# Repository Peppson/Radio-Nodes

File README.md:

# radio-nodes

Solar/Battery/USB powered wireless "smarthome" modules, based on the Attiny824 microcontroller.  
Serves as the end-node of [MQTT-radio-gateway](https://github.com/Peppson/MQTT-radio-gateway).   
Written in C++ with PlatformIO framework.  

&nbsp;
## Project Overview
- Each node is easily configurable to perform various tasks, such as watering plants,   
turn on the coffeemaker, opening blinds, relaying sensor data, etc. 

- Power consumption was the main concern when designing this.   
Nodes consumes ∼`2mA` @ 3.3V in active mode, and as low as ∼`3uA` @ 3.3V while deepsleeping!  
Making it possible to power the nodes indefinitely from a small solarpanel.  
Measured and optimized using [Power Profiler Kit II](https://www.nordicsemi.com/Products/Development-hardware/Power-Profiler-Kit-2).  

- This project was primarily made for personal ***"needs"***. But it is open for use by anyone who finds it beneficial.  
Every ***node*** has it's own directory inside `src` and it's own enviroment, selected from `platformio.ini`.

&nbsp;
## Hardware and PCB  
Designed a compact PCB integrating a [TP4056](https://www.amazon.com/TP4056/s?k=TP4056) Li-ion/LiPo battery charger, an [NRF24L01+](https://www.amazon.com/s?k=nRF24L01%2B&crid=1VM0GXMUG7ISX&sprefix=nrf24l01%2B%2Caps%2C145&ref=nb_sb_noss_1) radio,   
and the [Attiny824](https://www.mouser.se/ProductDetail/Microchip-Technology/ATTINY824-SSF?qs=pUKx8fyJudA6%2F%2FVSNIlI1w%3D%3D) AVR microcontroller.  

KiCad files: [📂 _KiCad/](./_KiCad/)  
More images in: [📂 _images/](./_images/)  
&nbsp;
> [!WARNING]
> Current PCB is wrong. Q1, Q2 and Q3 are incorrectly connected. Will update soon™

&nbsp;
<details>
<summary>
    Schematic
</summary>  

&nbsp;

</details>

<details>
<summary>
    PCB layout 
</summary>  

&nbsp;
> 2-layer PCB, dimensions 42mm x 31mm.

</details>  

<details>
<summary>
    Power consumption in active mode 
</summary>  

&nbsp; 
> In active mode, the node toggles its radio `on` for 50ms and `off` for 950ms to minimize power usage.

</details>
  
#### PCB

#### Hardware

&nbsp;
## Nodes 
<details>
<summary>
    Nodes 1-10: Self watering plants (Solar/USB powered)  
</summary>

Uses a 3-5V waterpump and DIY capacative fluid-level sensor.  See link below.  
[Liquid Level Sensing Using Capacitive-to-Digital Converters](https://www.analog.com/en/analog-dialogue/articles/liquid-level-sensing-using-cdcs.html)  

The solar-powered variant uses the TP4056 to charge a 3.7V Li-ion/LiPo battery.  
While the USB variant skips that step and plugs directly into 5V (3.3V LDO onboard).  

#### Node 1 hardware:  

&nbsp;  

#### Node 1 water sensor linearity:    

> Sensor (Adc) readings vs water level in %. 

&nbsp;  
</details>

<details>
    <summary>
        Node 11: Mocca Master controller
    </summary>

Uses a SG90 servo mounted internally to toggle the `On/Off` button,   
and a hall-effect current sensor, to get the current state.  
> "Looks pretty neat when the button toggles all by itself :)"   

</details>

&nbsp;

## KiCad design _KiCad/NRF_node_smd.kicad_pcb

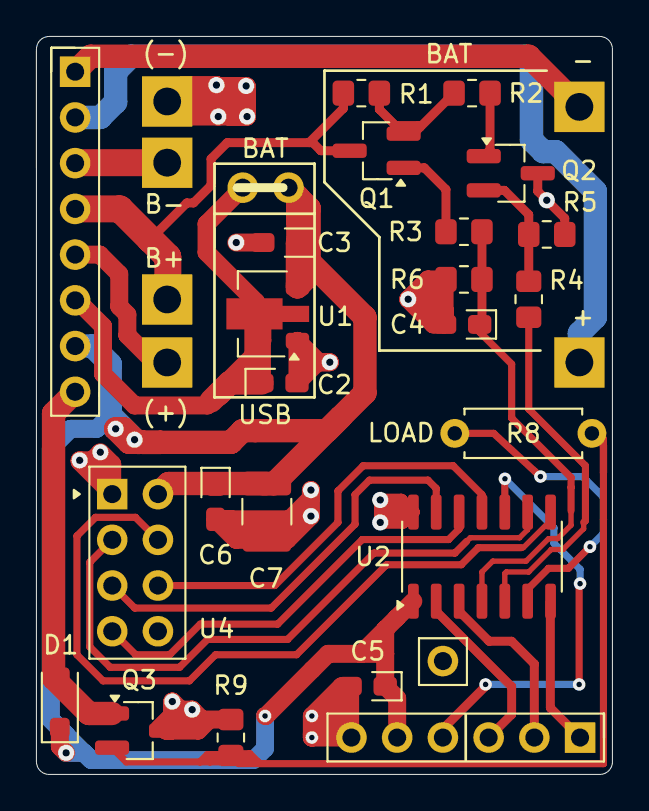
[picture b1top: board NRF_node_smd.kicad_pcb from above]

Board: 2 copper layers, 32.0 x 41.0 mm, 23 parts (0 on the bottom side), 22 nets.

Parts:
C2, C3: 1uf; CP_EIA-2012-15_AVX-P_Pad1.30x1.05mm_HandSolder
C4, C5, C6: 100nF; CP_EIA-2012-15_AVX-P_Pad1.30x1.05mm_HandSolder
C7: 22uF; C_1210_3225Metric_Pad1.33x2.70mm_HandSolder
D1: D; D_SOD-123F
J6: Conn_01x06; PinHeader_1x06_P2.54mm_Vertical
Q1: NTR4101PT1G; SOT-23_Handsoldering
Q2, Q3: PMV16XNR; SOT-23_Handsoldering
R1, R5: 100K; R_0805_2012Metric_Pad1.20x1.40mm_HandSolder
R2, R4, R6, R9: 10K; R_0805_2012Metric_Pad1.20x1.40mm_HandSolder
R3: 3K3; R_0805_2012Metric_Pad1.20x1.40mm_HandSolder
R8: 0-10K ?; R_Axial_DIN0207_L6.3mm_D2.5mm_P7.62mm_Horizontal
TP4056: TP4056-18650
U1: MCP1700T-3302E/MB; SOT-89-3
U2: ATtiny84A-P; SOIC-14_3.9x8.7mm_P1.27mm
U4: NRF24L01_Breakout; nRF24L01_Breakout

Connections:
/CE: U2.9 (PB0), U4.3 (CE)
/MISO: U2.12 (PA2), U4.7 (MISO)
/MOSI: U2.11 (PA1), U4.6 (MOSI)
/SCK: U2.13 (PA3), U4.5 (SCK)
/SS: U2.8 (PB1), U4.4 (~CSN)
ADC_ENABLED: R4.1, U2.5 (PA7)
ADC_MEASURE: C4.1, R3.2, R6.1, U2.4 (PA6)
BATTERY_VOLT: Q1.3 (S), R1.1, TP4056.5 (BAT(+))
GND: C2.2, C3.2, C4.2, C5.2, C6.2, C7.2, J6.6, Q2.3 (S), Q3.3 (S), R5.2, R6.2, R9.2, TP4056.3 (GND), U1.1 (GND), U2.14 (GND), U4.1 (GND)
LOAD_DRIVER_PIN: R8.1, U2.6 (PB3)
unnamed: D1.2 (A), Q3.1 (D)
unnamed: C2.1, U1.2 (VI)
unnamed: Q1.1 (D), R3.1
unnamed: Q1.2 (G), R1.2, R2.1
unnamed: Q2.1 (D), R2.2
unnamed: Q2.2 (G), R4.2, R5.1
unnamed: Q3.2 (G), R8.2, R9.1
PB2: J6.1, U2.7 (PB2)
PB4: J6.3, U2.2 (PA4)
PB5: J6.2, U2.3 (PA5)
UPDI: J6.4, U2.10 (~RESET/PA0)
VCC: C3.1, C5.1, C6.1, C7.1, D1.1 (K), J6.5, U1.3 (VO), U2.1 (VCC), U4.2 (VCC)

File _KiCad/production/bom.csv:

Designator,Footprint,Quantity,Value,LCSC Part #
"C2, C3",CP_EIA-2012-15_AVX-P_Pad1.30x1.05mm_HandSolder,2,1uf,
"C4, C5, C6",CP_EIA-2012-15_AVX-P_Pad1.30x1.05mm_HandSolder,3,100nF,
C7,1210,1,22uF,
D1,D_SOD-123F,1,D,
J6,PinHeader_1x06_P2.54mm_Vertical,1,Conn_01x06,
Q1,SOT-23_Handsoldering,1,NTR4101PT1G ,
"Q2, Q3",SOT-23_Handsoldering,2,PMV16XNR ,
"R1, R5",0805,2,100K,
"R2, R4, R6, R9",0805,4,10K,
R3,0805,1,3K3,
R8,R_Axial_DIN0207_L6.3mm_D2.5mm_P7.62mm_Horizontal,1,0-10K ?,
TP4056,TP4056-18650,1,~,
U1,SOT-89-3,1,MCP1700T-3302E/MB ,
U2,SOIC-14_3.9x8.7mm_P1.27mm,1,ATtiny84A-P,
U4,nRF24L01_Breakout,1,NRF24L01_Breakout,

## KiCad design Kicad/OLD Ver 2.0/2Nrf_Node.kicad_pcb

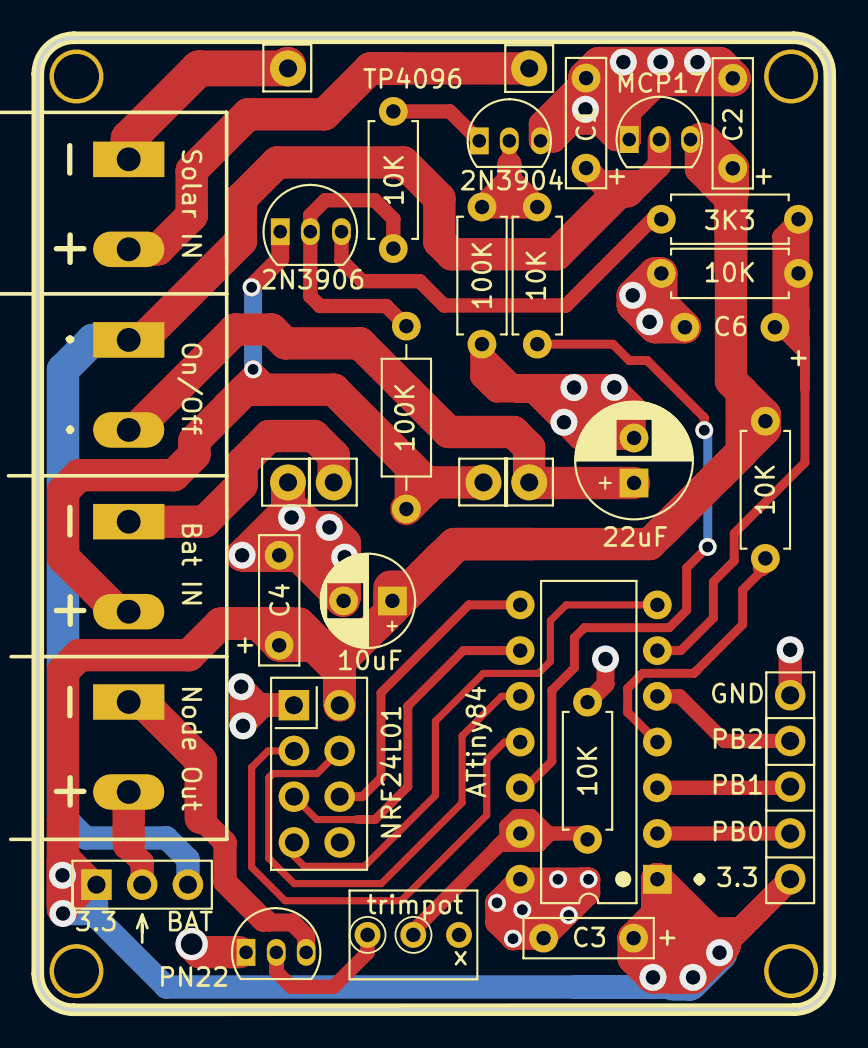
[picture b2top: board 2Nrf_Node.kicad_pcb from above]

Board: 2 copper layers, 44.0 x 54.0 mm, 32 parts (0 on the bottom side), 26 nets.

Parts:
10K: 10K; R_Axial_DIN0207_L6.3mm_D2.5mm_P7.62mm_Horizontal
C1, C2: 1uf; C_Rect_L7.0mm_W2.0mm_P5.00mm
C3, C4, C6: 100nF; C_Rect_L7.0mm_W2.0mm_P5.00mm
C5: 22uF; CP_Radial_D6.3mm_P2.50mm
C7: 10uF; CP_Radial_D5.0mm_P2.50mm
H1, H2, H4, H4#2: MountingHole; TestPoint_Keystone_5010-5014_Multipurpose
J1, J2, J3, J4: Terminal Block; TerminalBlock_Altech_AK300-2_P5.00mm
Pins: PinHeader_1x03_P2.54mm_Vertical
Q1: PN2222A; TO-92_Inline
Q2: 2N3906; TO-92_Inline
Q3: 2N3904; TO-92_Inline
R1: 3K3; R_Axial_DIN0207_L6.3mm_D2.5mm_P7.62mm_Horizontal
R2, R3, R6, R9: 10K; R_Axial_DIN0207_L6.3mm_D2.5mm_P7.62mm_Horizontal
R7: 100K; R_Axial_DIN0207_L6.3mm_D2.5mm_P7.62mm_Horizontal
R8: 100K; R_Axial_DIN0207_L6.3mm_D2.5mm_P10.16mm_Horizontal
SW2: SW_SPDT; PinHeader_1x03_P2.54mm_Vertical
TP4056: TP4056-Module
U1: MCP1700x-330xxTO; TO-92_Inline
U2: ATtiny84A-P; DIP-14_W7.62mm
U3: NRF24L01_Breakout; nRF24L01_Breakout

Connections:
1234: Q3.1 (E), R9.2
+3.3V: 10K.2, C2.1, C3.1, C4.1, C7.1, Pins.5, SW2.1 (A), U1.3 (VO), U2.1 (VCC), U3.2 (VCC)
/CE: U2.11 (PA2), U3.3 (CE)
/CSN: U2.10 (PA3), U3.4 (~CSN)
/MISO: U2.7 (PA6), U3.7 (MISO)
/MOSI: U2.8 (PA5), U3.6 (MOSI)
/SCK: U2.9 (PA4), U3.5 (SCK)
ADC_Enable: R6.1, U2.12 (PA1)
ADC_Measure: C6.1, R1.2, R2.1, U2.6 (PA7)
BAT_-: J3.1, TP4056.6 (VCC_OUT)
BAT_V: Q2.1 (E), R8.1, TP4056.5 (BAT(+))
GND: C1.2, C2.2, C3.2, C4.2, C5.2, C6.2, C7.2, Pins.1, Q1.1 (E), Q3.3 (C), R2.2, R3.1, R7.2, TP4056.4 (BAT(-)), U1.1 (GND), U2.14 (GND), U3.1 (GND)
unnamed: J4.2, SW2.2 (B)
unnamed: J4.1, Q1.3 (C)
unnamed: Pins.2, U2.5 (PB2)
unnamed: Pins.4, U2.2 (XTAL1/PB0)
unnamed: Pins.3, U2.3 (XTAL2/PB1)
unnamed: R3.2, U2.13 (AREF/PA0)
unnamed: Q2.2 (B), R8.2, R9.1
unnamed: Q2.3 (C), R1.1
unnamed: Q3.2 (B), R6.2, R7.1
unnamed: 10K.1, U2.4 (~RESET/PB3)
tp_+: J1.2, TP4056.1 (VCC_IN)
tp_-: J1.1, TP4056.2 (GND)
tp_out_+: C5.1, J2.2, TP4056.3 (GND)
tp_out_++: C1.1, J2.1, SW2.3 (C), U1.2 (VI)

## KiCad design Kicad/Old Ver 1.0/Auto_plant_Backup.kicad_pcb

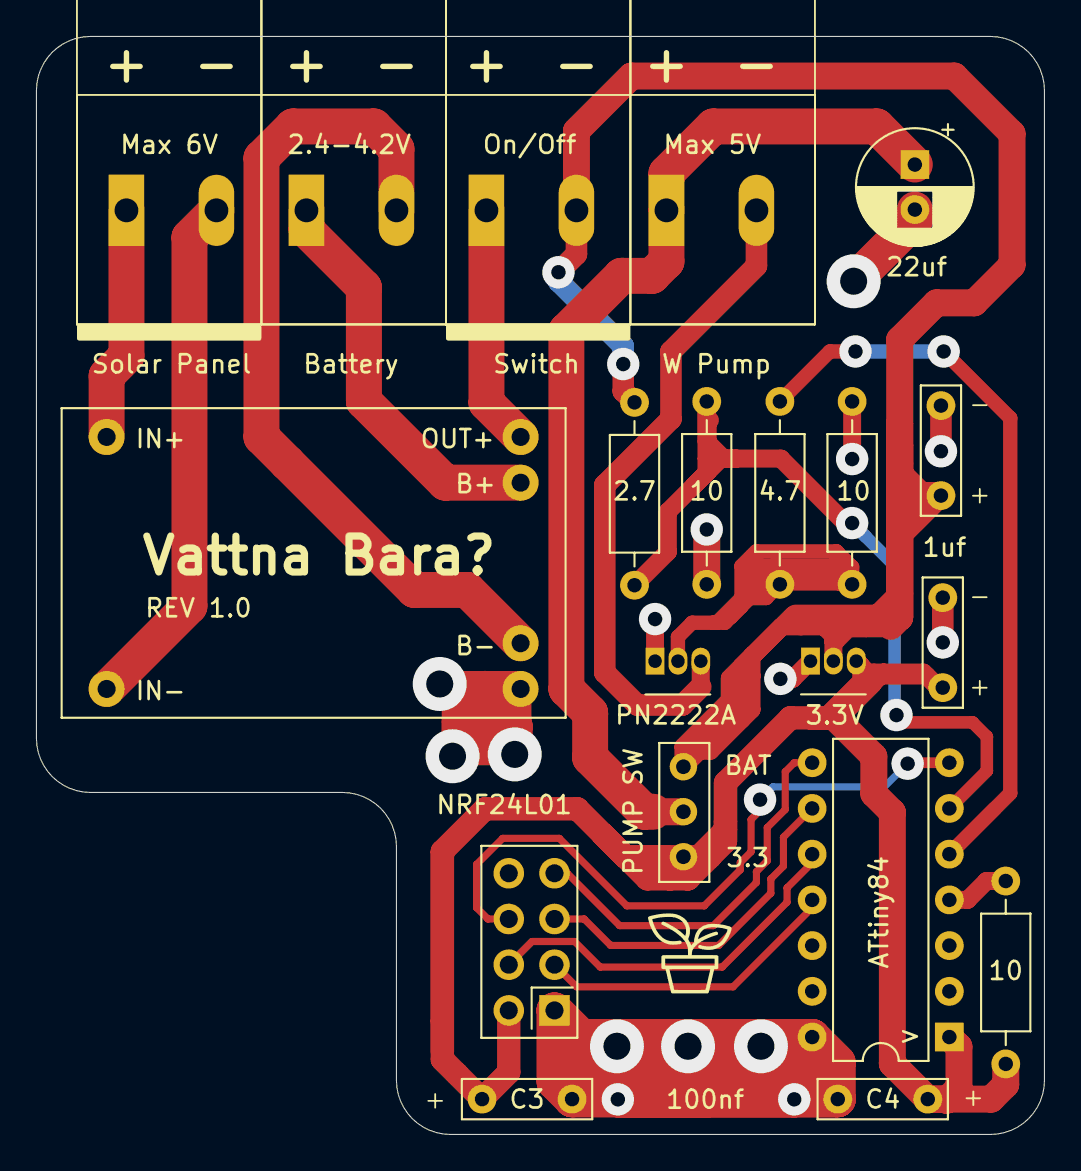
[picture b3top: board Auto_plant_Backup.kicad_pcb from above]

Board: 2 copper layers, 56.0 x 61.0 mm, 20 parts (0 on the bottom side), 19 nets.

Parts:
2.7: 2.7k; R_Axial_DIN0207_L6.3mm_D2.5mm_P10.16mm_Horizontal
3.3V: MCP1700x-330xxTO; TO-92_Inline
4.7, 10#3: 4.7k; R_Axial_DIN0207_L6.3mm_D2.5mm_P10.16mm_Horizontal
10, 10#2: 10k; R_Axial_DIN0207_L6.3mm_D2.5mm_P10.16mm_Horizontal
22uf: CP_Radial_D6.3mm_P2.50mm
100nf: 100nf; C_Rect_L7.0mm_W2.0mm_P5.00mm
+: Switch; TerminalBlock_Altech_AK300-2_P5.00mm
+#2: W Pump; TerminalBlock_Altech_AK300-2_P5.00mm
+#3: Battery; TerminalBlock_Altech_AK300-2_P5.00mm
-: Solar Panel; TerminalBlock_Altech_AK300-2_P5.00mm
ATtiny84: DIP-14_W7.62mm
C1, C2: 1uf; C_Rect_L7.0mm_W2.0mm_P5.00mm
C4: 100nf; C_Rect_L7.0mm_W2.0mm_P5.00mm
NRF24L01: NRF24L01_Breakout; nRF24L01_Breakout
PN2222A: PN2222A; TO-92_Inline
SW2: SW_SPDT; 2_way_switch
TP4056: TP4056-Module

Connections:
+3.3V: 3.3V.3 (VO), 10#3.2, 100nf.1, ATtiny84.1, C2.1, C4.1, NRF24L01.2 (VCC), SW2.1 (A)
/CE: ATtiny84.11, NRF24L01.3 (CE)
/MISO: ATtiny84.8, NRF24L01.7 (MISO)
/MOSI: ATtiny84.7, NRF24L01.6 (MOSI)
/SCK: ATtiny84.9, NRF24L01.5 (SCK)
BAT_V: 2.7.1, 3.3V.2 (VI), +.2, C1.1, SW2.3 (C)
CSN: ATtiny84.10, NRF24L01.4 (~CSN)
GND: 3.3V.1 (GND), 10.2, 10#2.2, 22uf.2, 100nf.2, ATtiny84.14, C1.2, C2.2, C4.2, NRF24L01.1 (GND), PN2222A.1 (E), TP4056.4 (BAT(-))
unnamed: -.2, TP4056.2 (GND)
unnamed: -.1, TP4056.1 (VCC_IN)
unnamed: +#3.2, TP4056.6 (VCC_OUT)
unnamed: +#3.1, TP4056.5 (BAT(+))
unnamed: +.1, TP4056.3 (GND)
unnamed: +#2.2, PN2222A.3 (C)
unnamed: 4.7.2, 10#2.1, PN2222A.2 (B)
unnamed: 4.7.1, ATtiny84.5
PA1: 2.7.2, 10.1, ATtiny84.6
P_OUT: 22uf.1, +#2.1, SW2.2 (B)
RESET: 10#3.1, ATtiny84.RESET

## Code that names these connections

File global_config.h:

#pragma once 
#include <Arduino.h>
#include <avr/io.h>
#include <avr/sleep.h>
#include <avr/wdt.h>
#include <avr/interrupt.h>
#include <stdint.h>


// Dev
#define USB_SERIAL_ENABLED 0                                // Serial TX 
#define DEBUG_LOOP_ENABLED 0                                // Enter debug_loop()
#define ADC_CAL_ENABLED 0                                   // Battery ADC calibration
#define PUMP_CAL_ENABLED 0                                  // Water pump calibration
#define SERVO_CAL_ENABLED 0                                 // Servo calibration
#define WATCHDOG_ENABLED 1                                  // Onboard Watchdog

// NRF24L01+ radio
#define RF24_THIS_ADDRESS NODE_ID                           // Radio address (env var from platformio.ini)
#define RF24_MASTER_ADDRESS 0                               // Address of master (0)
#define RF24_ON_TIME 50                                     // Active
#define RF24_OFF_TIME 950                                   // Sleeping                                  
#define RF24_CHANNEL 120                                    // Channel 1-126 (check with RF24/examples/scanner/scanner.ino) (120)
#define RF24_OUTPUT (RF24_PA_MAX)                           // Output level: RF24_PA_MIN, RF24_PA_LOW, RF24_PA_HIGH, RF24_PA_MAX, ERROR
#define RF24_DATARATE (RF24_250KBPS)                        // Datarate: RF24_2MBPS, RF24_1MBPS, RF24_250KBPS
#define RF24_PIPE 1                                         // Pipe address (1)

// Misc
#define SLEEP_RTC_INTERVAL_SECONDS 64.299f                  // Calibrated Average time between RTC interrupts while deepsleeping (s)
#define WATER_PUMP_RUNTIME_MAX 10                           // Maximum time the waterpump is allowed to run (s) if a flowerpot node


/*
-------------------------- ATtiny824 Pinout --------------------------                                   

                         VCC  1|o   |14 GND                        
             PWM/ADC --- PA4  2|    |13 PA3 --- RF24 SCK          
             PWM/ADC --- PA5  3|    |12 PA2 --- RF24 MISO  
                 ADC --- PA6  4|    |11 PA1 --- RF24 MOSI           
                 ADC --- PA7  5|    |10 PA0 --- UPDI programming          
           Power I/O --- PB3  6|    |9  PB0 --- RF24 CE          
       TX Serial out --- PB2  7|    |8  PB1 --- RF24 CSN  

----------------------------------------------------------------------
*/
#define PIN_CE                  PIN_PB0         // Nrf24l01 Ce pin
#define PIN_CSN                 PIN_PB1         // Nrf24l01 CSN pin
#define PIN_UPDI                PIN_PB0         // UPDI programming
#define PIN_POWER_IO            PIN_PB3         // Controls the "power circuit" (battery > load > Nfet > gnd)
#define PIN_TX_SERAIL           PIN_PB2         // Serial out TX


// Watchdog
#if WATCHDOG_ENABLED
    #define WDT_FEED() __asm__ __volatile__ ("wdr") 
    #define WDT_ENABLE() _PROTECTED_WRITE(WDT.CTRLA, WDT_PERIOD_4KCLK_gc)
    #define WDT_DISABLE() wdt_disable()
#else
    #define WDT_FEED()
    #define WDT_ENABLE()
    #define WDT_DISABLE()
#endif


// Logging
#if USB_SERIAL_ENABLED
    #define log(...) Serial.printf(__VA_ARGS__)
    #define STOP log("\n-----  STOP  ----- \n"); while (1) { WDT_FEED(); delay(1000); }
#else
    #define log(...)
    #define STOP
#endif


// Include selected node's "node_config.h" into global space (a bit hacky?)
#if NODE_ID == 1
    #include "src/01_solar_self_watering_plant/node_config.h"
#elif NODE_ID == 2
    #include "src/02_solar_self_watering_plant/node_config.h"
#elif NODE_ID == 3
    #include "src/03_solar_self_watering_plant/node_config.h"
#elif NODE_ID == 5
    #include "src/05_USB_self_watering_plant/node_config.h"
#elif NODE_ID == 6
    #include "src/06_USB_self_watering_plant/node_config.h"
#elif NODE_ID == 7
    #include "src/07_USB_self_watering_plant/node_config.h"
#elif NODE_ID == 11
    #include "src/11_moccamaster/node_config.h"
#elif NODE_ID == 255
    // Debug
#else
    #error "Unknown NODE_ID, check platformio.ini"
#endif


// CALIBRATION true if any if the calibration macros are set
#if DEBUG_LOOP_ENABLED || ADC_CAL_ENABLED || PUMP_CAL_ENABLED || SERVO_CAL_ENABLED
    #define CALIBRATION true
#else 
    #define CALIBRATION false
#endif

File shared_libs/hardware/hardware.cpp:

#include "hardware.h"
#include "utility.h"
#include "../shared_libs/rf24_radio/rf24_radio.h"


// Members
uint32_t Hardware::deepsleep_timestamp = 0; 
uint32_t Hardware::send_data_timestamp = 0;    
uint8_t Hardware::pin_ADC_enable;
uint8_t Hardware::pin_ADC_measure;
RF24Radio* Hardware::_radio_ptr;
volatile bool _lightsleep_wakeup;


// RTC Interrupt handler. Wakes up the CPU periodically while deepsleeping
// Only way to timekeep while deepsleeping
ISR (RTC_CNT_vect) {
    RTC.INTFLAGS |= RTC_OVF_bm;
    _lightsleep_wakeup = true;
}


// Helper
constexpr uint32_t convert_hhmm_to_seconds(const uint32_t& value) {
    static_assert(selected_node::SLEEP_AT_THIS_TIME >= 0 
        && selected_node::SLEEP_AT_THIS_TIME <= 2400, "Node time must follow \"hhmm\" format");

    uint32_t hour = value / 100;  
    uint32_t minute = value % 100; 

    return (hour*60*60) + (minute*60);
}


void Hardware::begin(RF24Radio* radio_ptr) {
    #if USB_SERIAL_ENABLED
        init_USB_serial();
    #endif

    // Helps with uploading if CPU is stuck "RSP_ILLEGAL_MCU_STATE"
    delay(3000);

    // Enable Watchdog at max interval ≈ 4s 
    WDT_ENABLE();
    WDT_FEED();

    // Save pointer to radio
    _radio_ptr = radio_ptr; 

    // I/O pins
    pinMode(PIN_POWER_IO, OUTPUT);
    digitalWrite(PIN_POWER_IO, LOW);
    pinMode(PIN_UPDI, INPUT_PULLUP);

    // Disable unused peripherals
    ADC0.CTRLA &= ~ADC_ENABLE_bm;   // ADC 
    TWI0.CTRLA &= ~TWI_ENABLE_bm;   // I2C
    CCL.CTRLA &= ~CCL_ENABLE_bm;    // CCL
}


void Hardware::init_USB_serial() {
    Serial.begin(9600, (SERIAL_8N1 | SERIAL_TX_ONLY));
    while (!Serial) { }
    delay(100);
    log("\n-- Node %i --\n", RF24_THIS_ADDRESS);
}


void Hardware::restart_device() { 
    // Wait for Watchdog to reset board
    _PROTECTED_WRITE(WDT.CTRLA, WDT_PERIOD_4KCLK_gc);
    while (1) { } 
}


void Hardware::deepsleep(uint32_t sleep_duration_s) {
    const uint16_t sleep_limit = sleep_duration_s / SLEEP_RTC_INTERVAL_SECONDS;
    volatile uint16_t sleep_counter = 0;

    disable_all_peripherals();
    WDT_DISABLE();

    //
    // Enable periodic RTC interrupts to allow the CPU to wake up from sleep
    // Average time between interrupts = 64.299 seconds
    // Will continue to sleep until (sleep_counter * 64.299) > SLEEP_DURATION_SECONDS
    // 
  
    RTC.PER = 0xFFFF;                               // Set period: 1-65535 (0XFFFF longest possible interval)
    RTC.CLKSEL = RTC_CLKSEL_INT1K_gc;               // Set 1kHz internal clock as source
    RTC.INTCTRL |= RTC_OVF_bm;                      // Interrupt when period overflows
    RTC.CTRLA = RTC_RTCEN_bm | RTC_RUNSTDBY_bm;     // Enable + active in SLEEP_MODE_STANDBY

    // ZZZZzzzzZzzzzZzz
    set_sleep_mode(SLEEP_MODE_STANDBY);
    sleep_enable();
    sleep_cpu();

    // Continue to sleep for sleep_duration_s
    while (sleep_counter < sleep_limit) {
        sleep_counter++;    
        RTC.CNT = 0; // Reset timer
        sleep_cpu();
    }
        
    // Wake up
    sleep_disable();
    restart_device(); // Full reset
}


void Hardware::lightsleep(uint16_t sleep_duration_ms) {
    WDT_FEED();

    if (sleep_duration_ms >= 35*1000) {     // Dont allow longer sleep than the watchdog timeout
        sleep_duration_ms = 35*1000; 
    }

    // Same behavior as deepsleep()
    RTC.PER = sleep_duration_ms;            // Set period: 1-65535 
    RTC.CLKSEL = RTC_CLKSEL_INT1K_gc;       // Set 1kHz internal clock as source
    RTC.INTCTRL |= RTC_OVF_bm;              // Interrupt when period overflows
    RTC.CTRLA = RTC_RTCEN_bm;               // Enable
    RTC.CNT = 0;                            // Reset RTC

    // ZZZZzzzzZzzzzZzz
    _lightsleep_wakeup = false; 
    set_sleep_mode(SLEEP_MODE_IDLE);
    sleep_enable();
    sleep_cpu();

    // Continue to lightsleep for sleep_duration_ms
    // TCB 0 and 1 interrupts alot, only wake up from RTC interrupt 
    while (!_lightsleep_wakeup) {    
        WDT_FEED();
        sleep_cpu();
    }

    // Wake up
    RTC.INTCTRL &= ~RTC_OVF_bm; // Disable RTC interrupt
    sleep_disable();
    WDT_FEED();
}


void Hardware::disable_all_peripherals() {
    if (_radio_ptr) {
        _radio_ptr->power_down();
        delay(2000); // Needed!
        _radio_ptr->~RF24Radio();
    }

    // Cpu
    ADC0.CTRLA &= ~ADC_ENABLE_bm;                   // ADC
    SPI0.CTRLA &= ~SPI_ENABLE_bm;                   // SPI 
    TWI0.CTRLA &= ~TWI_ENABLE_bm;                   // I2C
    CCL.CTRLA &= ~CCL_ENABLE_bm;                    // CCL (Configurable Custom Logic)
    TCA0.SINGLE.CTRLA &= ~TCA_SINGLE_ENABLE_bm;     // TCA0 timer
    TCB0.CTRLA &= ~TCB_ENABLE_bm;                   // TCB0 timer

    // Disable all pins (all except UPDI)
    pinMode(PIN_PA4, INPUT_PULLUP);
    pinMode(PIN_PA5, INPUT_PULLUP);
    pinMode(PIN_PA6, INPUT_PULLUP);
    pinMode(PIN_PA7, INPUT_PULLUP);
    pinMode(PIN_PB3, INPUT_PULLUP);
    pinMode(PIN_PB2, INPUT_PULLUP);
    pinMode(PIN_PA1, INPUT_PULLUP);
    pinMode(PIN_PA2, INPUT_PULLUP);
    pinMode(PIN_PA3, INPUT_PULLUP);
    pinMode(PIN_PB0, INPUT_PULLUP);
    pinMode(PIN_PB1, INPUT_PULLUP);

    // Current draw while sleeping with Serial enable = 3uA, about 80uA if Serial is disable
    // So just quickly enable it before sleeping. Have not found exactly why it behaves like this... 
    #if !USB_SERIAL_ENABLED
        init_USB_serial();  
    #endif
}


void Hardware::timeout(uint32_t timeout_ms) {
    uint32_t end_time = millis() + timeout_ms;

    while (millis() < end_time) {
        WDT_FEED();
        delay(10);
    }
}


uint16_t Hardware::get_remaining_battery_charge() { 
    constexpr uint8_t samples = 100;
    WDT_FEED();

    // Enable ADC and toggle on mosfet pair to allow current to ADC
    ADC0.CTRLA |= ADC_ENABLE_bm;
    digitalWrite(pin_ADC_enable, HIGH);

    // Sum ADC readings (0-1023)
    uint32_t sum = 0;
    for (size_t i = 0; i < samples; i++) {
        uint16_t level = analogRead(pin_ADC_measure); 
        sum += constrain(level, 0, 1023);
        delay(1);
    } 

    // Turn off ADC and close connection to battery
    digitalWrite(pin_ADC_enable, LOW);
    ADC0.CTRLA &= ~ADC_ENABLE_bm;

    return sum / samples;
}


bool Hardware::set_time_until_deepsleep(uint16_t time_input) { 
    if (!verify_time_input(time_input)) { 
        return false; 
    }

    // Convert to seconds
    constexpr uint32_t sleep_at_this_time = convert_hhmm_to_seconds(selected_node::SLEEP_AT_THIS_TIME);
    uint32_t current_time = convert_hhmm_to_seconds(time_input);

    // Is current time inside the "sleep window"? If so, how long should we sleep?
    // Case before midnight 
    if (current_time >= sleep_at_this_time) {
        uint32_t offset = current_time - sleep_at_this_time;
        uint32_t sleep_duration_s = selected_node::SLEEP_DURATION_SECONDS - offset;   
        deepsleep(sleep_duration_s);

    // Case after midnight
    } else if (current_time < sleep_at_this_time - selected_node::SLEEP_DURATION_SECONDS) {
        uint32_t sleep_duration_s = sleep_at_this_time - current_time - selected_node::SLEEP_DURATION_SECONDS;
        deepsleep(sleep_duration_s);

    // Outside "sleep window". Set time until "selected_node::SLEEP_AT_THIS_TIME"
    } else {
        uint32_t time_left_ms = (sleep_at_this_time - current_time) * 1000UL;   // Convert to milliseconds
        deepsleep_timestamp = time_left_ms + millis();                          // Add current time for absolute timestamp
    }

    return true;
}


bool Hardware::verify_time_input(const uint16_t time) {
    return (time >= 0 && time <= 2400);
}


/* 
void Hardware::print_time(const uint32_t& time_left) {
    uint32_t hour = (time_left / (60 * 60)) % 24;
    uint32_t minute = (time_left / 60) % 60;

    log("hour left: %i\n", hour);
    log("minute left: %i\n", minute);
} 
*/

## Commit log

2023-07-22 remove
2023-07-25 Create .clang-format
